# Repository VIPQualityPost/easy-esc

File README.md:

# easy-esc
simple, small BLDC controller with FOC implementation from SimpleFOC on RP2040.

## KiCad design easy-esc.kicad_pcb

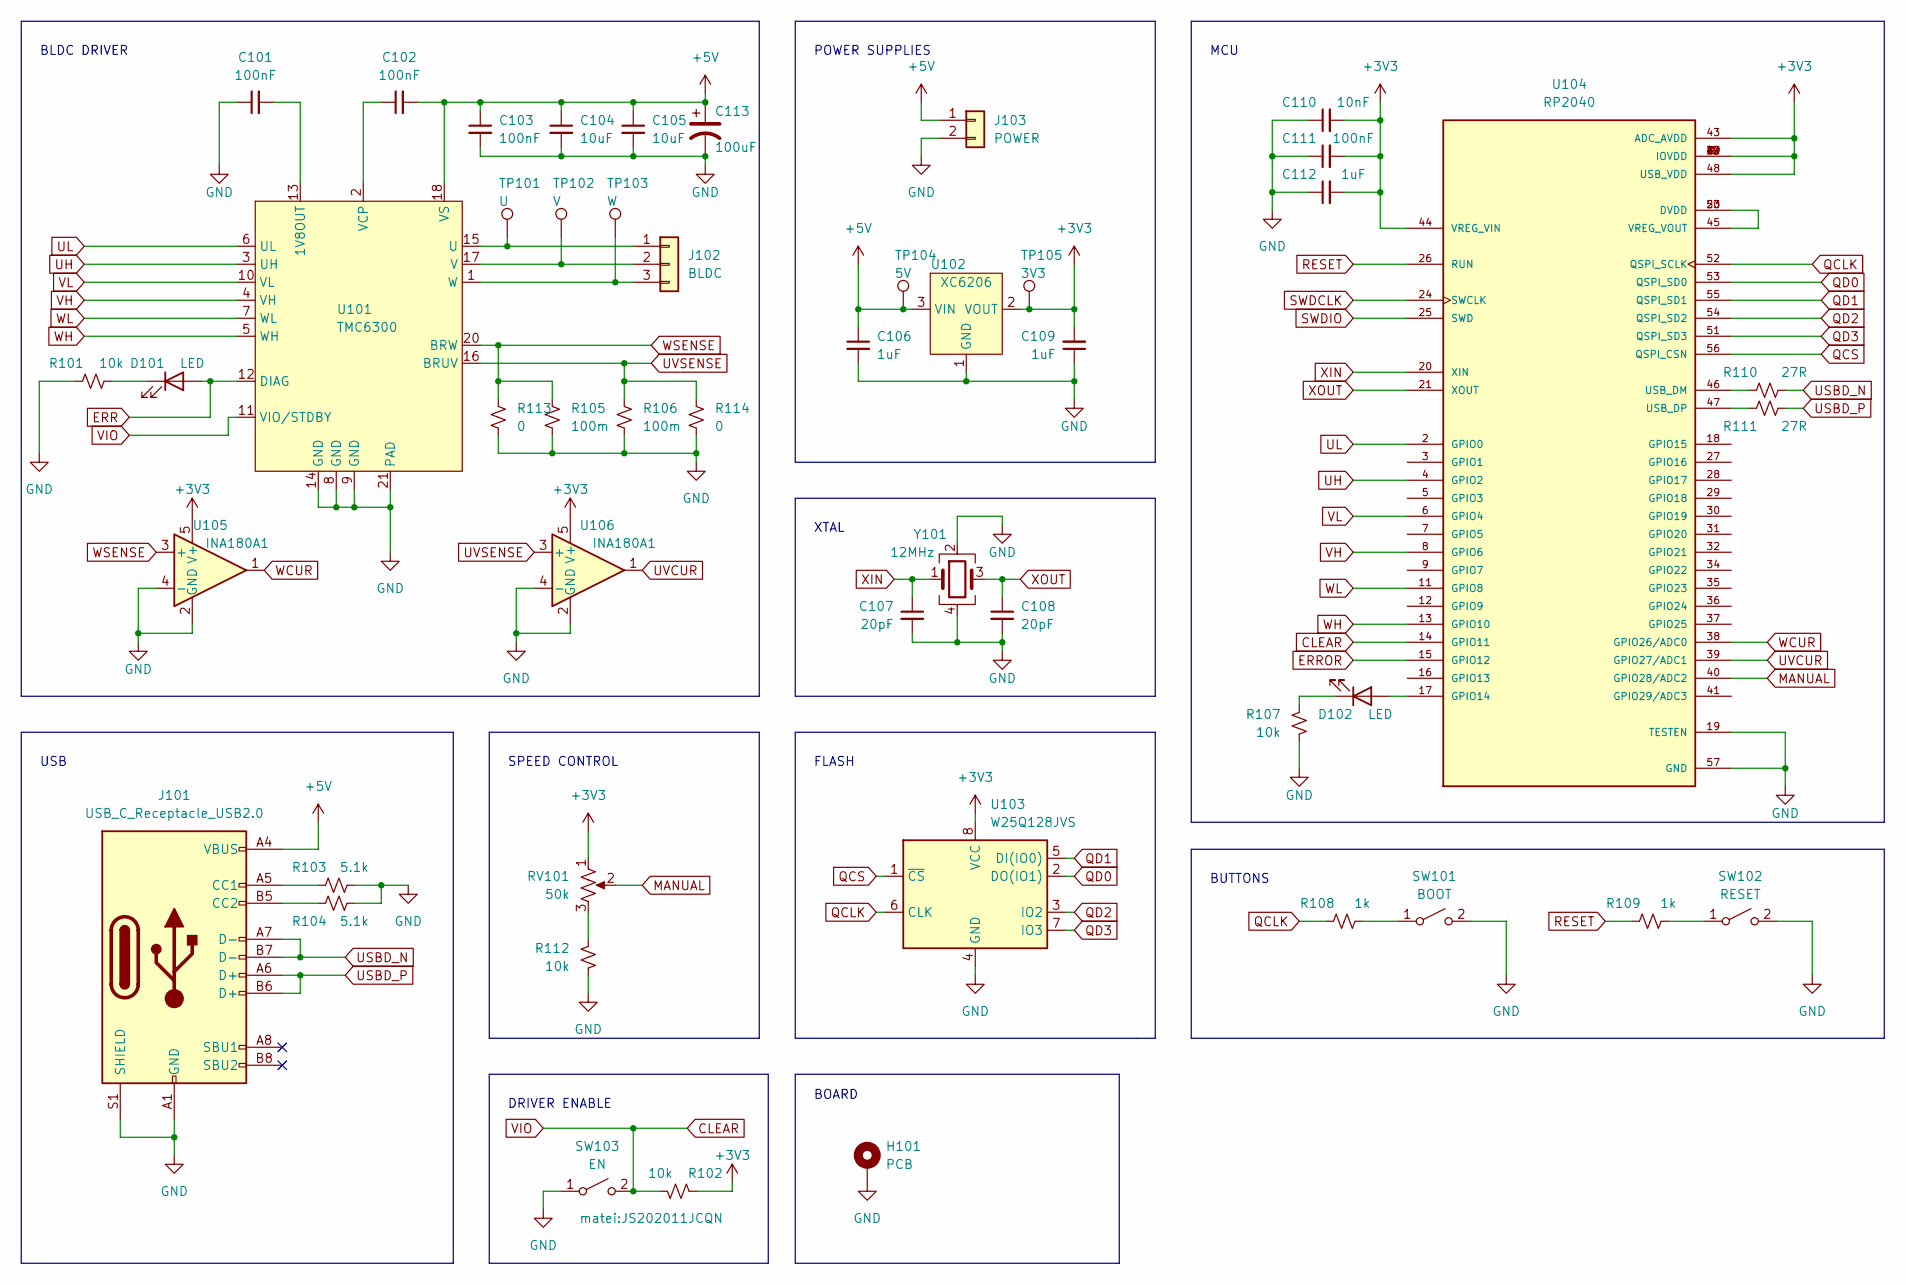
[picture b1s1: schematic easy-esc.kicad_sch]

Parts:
C101, C102, C103, C111: 100nF; C_0402_1005Metric
C104, C105: 10uF; C_0402_1005Metric
C106, C109, C112: 1uF; C_0402_1005Metric
C107, C108: 20pF; C_0402_1005Metric
C110: 10nF; C_0402_1005Metric
C113: 100uF; CP_Elec_4x3.9
D101, D102: LED; D_0603_1608Metric
H101: PCB; easy-esc-outline
J101: USB_C_Receptacle_USB2.0; USB_C_Receptacle_HRO_TYPE-C-31-M-12
J102: BLDC; JST_XH_S3B-XH-A_1x03_P2.50mm_Horizontal
J103: POWER; JST_XH_S2B-XH-A_1x02_P2.50mm_Horizontal
R101, R102, R107, R112: 10k; R_0402_1005Metric
R103, R104: 5.1k; R_0402_1005Metric
R105, R106: 100m; R_2512_6332Metric
R108, R109: 1k; R_0402_1005Metric
R110, R111: 27R; R_0603_1608Metric
R113, R114: 0; R_0402_1005Metric
RV101: 50k; Potentiometer_Bourns_3314J_Vertical
SW101: BOOT; TS-1187A-B-A-B
SW102: RESET; TS-1187A-B-A-B
SW103: EN; JS202011JCQN
TP101: U; TestPoint_Pad_D1.5mm
TP102: V; TestPoint_Pad_D1.5mm
TP103: W; TestPoint_Pad_D1.5mm
TP104: 5V; TestPoint_Pad_D1.5mm
TP105: 3V3; TestPoint_Pad_D1.5mm
U101: TMC6300; QFN-20-1EP_3x3mm_P0.4mm_EP1.65x1.65mm
U102: XC6206; SOT-23
U103: W25Q128JVS; SOIC-8_5.23x5.23mm_P1.27mm
U104: RP2040; QFN40P700X700X90-57N; PARTREV 1.6.1
U105, U106: INA180A1; SOT-23-5
Y101: 12MHz; Crystal_SMD_3225-4Pin_3.2x2.5mm

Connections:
+3V3: C109.2, C110.2, C111.2, C112.2, R102.1, RV101.1, TP105.1, U102.2 (VOUT), U103.8 (VCC), U104.1 (IOVDD), U104.10 (IOVDD), U104.22 (IOVDD), U104.33 (IOVDD), U104.42 (IOVDD), U104.43 (ADC_AVDD), U104.44 (VREG_VIN), U104.48 (USB_VDD), U104.49 (IOVDD), U105.5 (V+), U106.5 (V+)
+5V: C102.2, C103.1, C104.1, C105.1, C106.1, C113.1, J101.A4 (VBUS), J101.A9 (VBUS), J101.B4 (VBUS), J101.B9 (VBUS), J103.1, TP104.1, U101.18 (VS), U102.3 (VIN)
CLEAR: R102.2, SW103.2 (B), U101.11 (VIO/STDBY), U104.14 (GPIO11)
ERR: D101.2 (A), U101.12 (DIAG)
ERROR: U104.15 (GPIO12)
GND: C101.1, C103.2, C104.2, C105.2, C106.2, C107.2, C108.2, C109.1, C110.1, C111.1, C112.1, C113.2, H101.1, J101.A1 (GND), J101.A12 (GND), J101.B1 (GND), J101.B12 (GND), J101.S1 (SHIELD), J103.2, R101.1, R103.2, R104.2, R105.2, R106.2, R107.1, R112.1, R113.2, R114.2, SW101.2 (B), SW102.2 (B), SW103.1 (A), U101.8 (GND), U101.9 (GND), U101.14 (GND), U101.21 (PAD), U102.1 (GND), U103.4 (GND), U104.19 (TESTEN), U104.57 (GND), U105.2 (GND), U105.4 (-), U106.2 (GND), U106.4 (-), Y101.2, Y101.4
MANUAL: RV101.2, U104.40 (GPIO28/ADC2)
unnamed: C101.2, U101.13 (1V8OUT)
unnamed: C102.1, U101.2 (VCP)
unnamed: D101.1 (K), R101.2
unnamed: D102.1 (K), R107.2
unnamed: D102.2 (A), U104.17 (GPIO14)
unnamed: J101.A5 (CC1), R103.1
unnamed: J101.B5 (CC2), R104.1
unnamed: J102.1, TP101.1, U101.15 (U)
unnamed: J102.2, TP102.1, U101.17 (V)
unnamed: J102.3, TP103.1, U101.1 (W)
unnamed: R108.2, SW101.1 (A)
unnamed: R109.2, SW102.1 (A)
unnamed: R110.1, U104.46 (USB_DM)
unnamed: R111.1, U104.47 (USB_DP)
unnamed: R112.2, RV101.3
unnamed: U104.23 (DVDD), U104.45 (VREG_VOUT), U104.50 (DVDD)
QCLK: R108.1, U103.6 (CLK), U104.52 (QSPI_SCLK)
QCS: U103.1 (~CS), U104.56 (QSPI_CSN)
QD0: U103.2 (DO(IO1)), U104.53 (QSPI_SD0)
QD1: U103.5 (DI(IO0)), U104.55 (QSPI_SD1)
QD2: U103.3 (IO2), U104.54 (QSPI_SD2)
QD3: U103.7 (IO3), U104.51 (QSPI_SD3)
RESET: R109.1, U104.26 (RUN)
SWDCLK: U104.24 (SWCLK)
SWDIO: U104.25 (SWD)
UH: U101.3 (UH), U104.4 (GPIO2)
UL: U101.6 (UL), U104.2 (GPIO0)
USBD_N: J101.A7 (D-), J101.B7 (D-), R110.2
USBD_P: J101.A6 (D+), J101.B6 (D+), R111.2
UVCUR: U104.39 (GPIO27/ADC1), U106.1
UVSENSE: R106.1, R114.1, U101.16 (BRUV), U106.3 (+)
VH: U101.4 (VH), U104.8 (GPIO6)
VL: U101.10 (VL), U104.6 (GPIO4)
WCUR: U104.38 (GPIO26/ADC0), U105.1
WH: U101.5 (WH), U104.13 (GPIO10)
WL: U101.7 (WL), U104.11 (GPIO8)
WSENSE: R105.1, R113.1, U101.20 (BRW), U105.3 (+)
XIN: C107.1, U104.20 (XIN), Y101.1
XOUT: C108.1, U104.21 (XOUT), Y101.3

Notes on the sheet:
BUTTONS
BLDC DRIVER
BOARD
SPEED CONTROL
XTAL
MCU
USB
FLASH
POWER SUPPLIES
DRIVER ENABLE

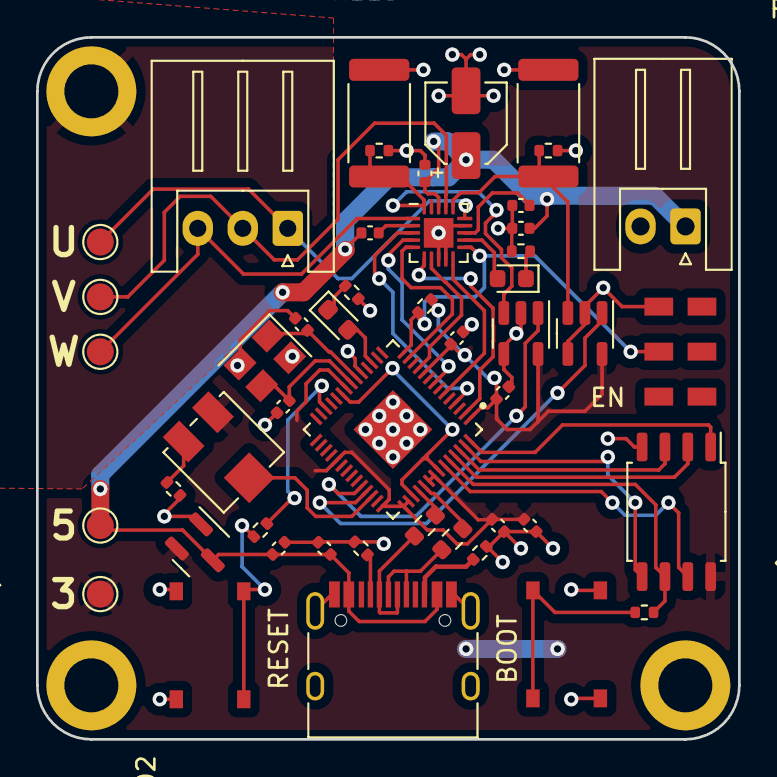
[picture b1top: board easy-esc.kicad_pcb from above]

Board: 2 copper layers, 39.0 x 39.0 mm, 49 parts (0 on the bottom side), 43 nets.

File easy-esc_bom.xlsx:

Ref | Qnty | Value | Footprint | MFG PN | LCSC PN | VENDOR
C101, C102, C103, C111, | 4.0 | 100nF | 0402_C | CC0402KRX7R8BB104 | C105883 | YAGEO
C104, C105, | 2.0 | 10uF | 0402_C | CL05A106MQ5NUNC | C15525 | Samsung Electro-Mechanics
C106, C109, C112, | 3.0 | 1uF | 0402_C | CL05A105KA5NQNC | C52923 | Samsung Electro-Mechanics
C107, C108, | 2.0 | 20pF | 0402_C | CC0402JRNPO9BN200 | C107000 | YAGEO
C110, | 1.0 | 10nF | 0402_C | CL05B103KB5NNNC | C15195 | Samsung Electro-Mechanics
D101, D102, | 2.0 | LED | 0603_D | 19-213/Y2C-CQ2R2L/3T(CY) | C72038 | Everlight Elec
J101, | 1.0 | USB_C_Receptacle_USB2.0 | HRO TYPE-C-31-M-12 | TYPE-C-31-M-12 | C165948 | Korean Hroparts Elec
R101, R102, R107, R112, | 4.0 | 10k | 0402_R | 0402WGF1002TCE | C25744 | UNI-ROYAL(Uniroyal Elec)
R103, R104, | 2.0 | 5.1k | 0402_R | 0402WGF5101TCE | C25905 | UNI-ROYAL(Uniroyal Elec)
R108, R109, | 2.0 | 1k | 0402_R | 0402WGF1001TCE | C11702 | UNI-ROYAL(Uniroyal Elec)
R110, R111, | 2.0 | 27R | 0603_R | 0603WAF270JT5E | C25190 | UNI-ROYAL(Uniroyal Elec)
R113, R114, | 2.0 | 0R | 0402_R | 0402WGF0000TCE | C17168 | UNI-ROYAL(Uniroyal Elec)
RV101, | 1.0 | 50k | Bourns 3314J | 3314J-1-503E | C50895 | BOURNS
SW101, SW102, | 1.0 | C318884 | TS-1187A-B-A-B | TS-1187A-B-A-B | C318884 | XKB Connectivity
U101, | 1.0 | TMC6300 | QFN20 | TMC6300-LA | C5196961 | Trinamic Motion Control
U102, | 1.0 | XC6206 | SOT-23 | XC6206-3.3V | C2891841 | YONGYUTAI
U103, | 1.0 | W25Q128JVS | SOIC-8 | W25Q128JVSIQ | C97521 | Winbond Elec
U104, | 1.0 | RP2040 | QFN56 | RP2040 | C2040 | Raspberry Pi
U105, U106, | 2.0 | INA180A1 | SOT-23-5 | INA180A1IDBVR | C122228 | Texas Instruments
Y101, | 1.0 | 12MHz | Crystal SMD 3225-4Pin_3.2x2.5mm | X322512MSB4SI | C9002 | Yangxing Tech

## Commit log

2022-12-14 finalize fab files
2022-12-14 finalize file sorting and renders
2022-12-14 clean up
2023-02-07 update repo
2023-02-13 Auto-commit Mon Feb 13 12:20:05 EST 2023
2023-02-13 Auto-commit Mon Feb 13 14:52:14 EST 2023
2023-02-13 removed ignore files
2023-02-17 Auto-commit Thu Feb 16 21:34:57 EST 2023
2023-02-17 Auto-commit Fri Feb 17 12:27:45 EST 2023
2023-02-17 Remove ignored files
2023-02-18 fix schematic and layout issues from V1 production run
2023-04-11 Auto-commit Tue Apr 11 10:47:13 EDT 2023
2023-04-30 Auto-commit Sun Apr 30 10:54:40 EDT 2023
